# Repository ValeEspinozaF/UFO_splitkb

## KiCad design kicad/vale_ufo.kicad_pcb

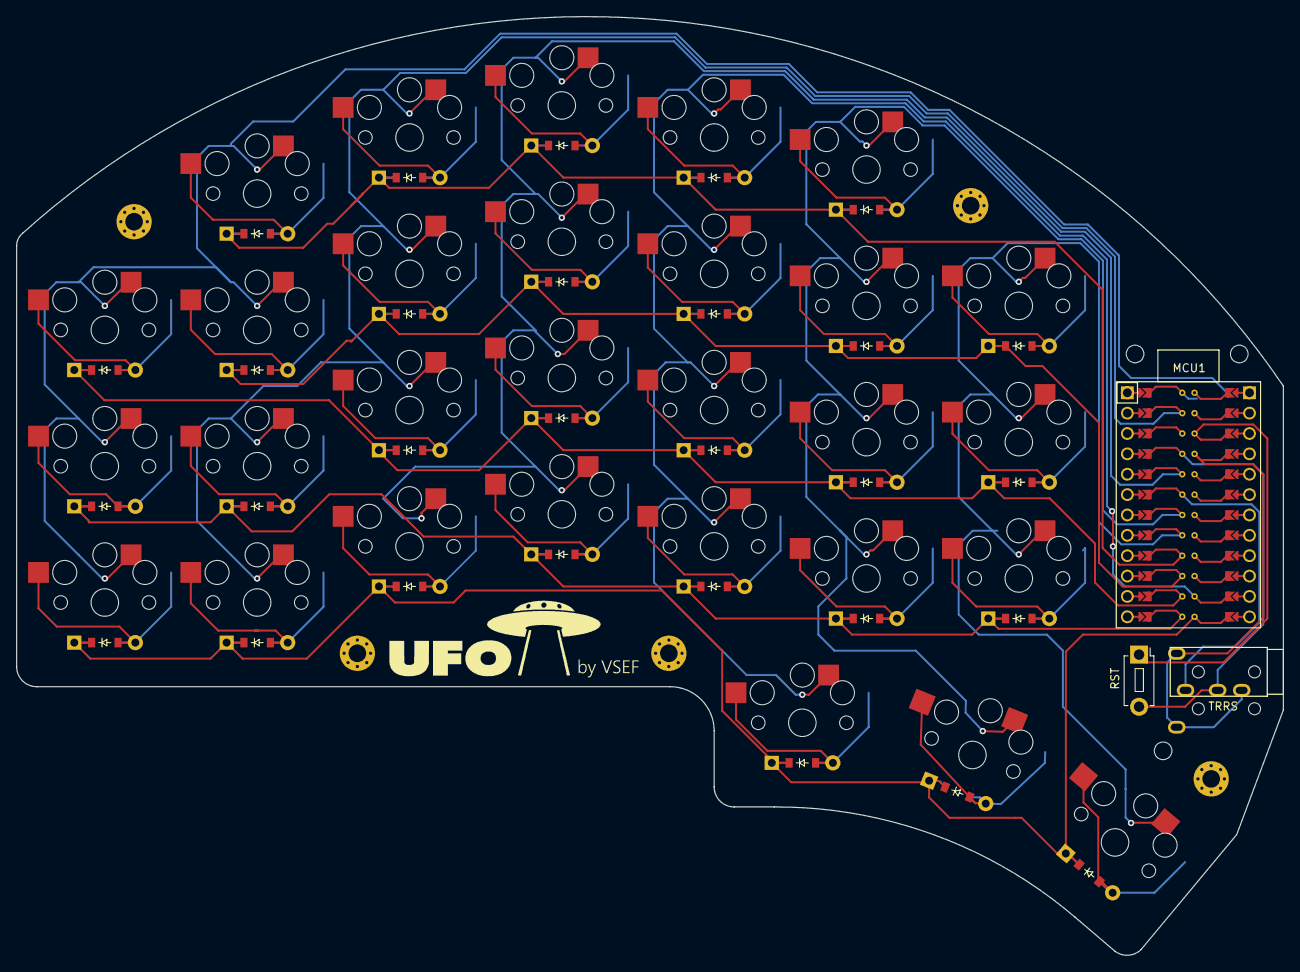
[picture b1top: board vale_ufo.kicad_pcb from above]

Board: 2 copper layers, 158.0 x 117.1 mm, 61 parts (0 on the bottom side), 44 nets.

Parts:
D1, D2, D3, D4, D5, D6, D7, D8, D9, D10, D11, D12, D13, D14, D15, D16, D17, D18, D19, D20, D21, D22, D23, D24, D25, D26, D27, D28, D29: ComboDiode
MCU1: ProMicro
RST: SW_PUSH_1P1T_6x3.5mm_H4.3_APEM_MJTP1243
S1, S2, S3, S4, S5, S6, S7, S8, S9, S10, S11, S12, S13, S14, S15, S16, S17, S18, S19, S20, S21, S22, S23, S24, S25, S26, S27, S28, S29: PG1350
TRRS: TRRS-PJ-320A-dual

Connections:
GND: MCU1.2, MCU1.21, MCU1.22, RST.2, TRRS.3
P0: MCU1.23, S4.1, S5.1, S9.1, S10.1, S11.1
P1: MCU1.24, S1.1, S2.1, S3.1, S6.1, S7.1
P2: MCU1.20, S8.1, S12.1, S13.1, S14.1, S15.1
P3: MCU1.19, TRRS.2
P4: MCU1.18, S20.1, S21.1, S22.1, S23.1, S28.1
P5: MCU1.17, S24.1, S25.1, S26.1, S29.1
P6: D7.1, D7.2, D11.1, D11.2, D15.1, D15.2, D19.1, D19.2, D23.1, D23.2, MCU1.16
P7: D6.1, D6.2, D10.1, D10.2, D14.1, D14.2, D18.1, D18.2, D22.1, D22.2, D26.1, D26.2, MCU1.15
P8: D3.1, D3.2, D9.1, D9.2, D13.1, D13.2, D17.1, D17.2, D21.1, D21.2, D25.1, D25.2, MCU1.14
P9: D2.1, D2.2, D5.1, D5.2, D12.1, D12.2, D16.1, D16.2, D20.1, D20.2, D24.1, D24.2, MCU1.13
P10: D1.1, D1.2, D4.1, D4.2, D8.1, D8.2, D27.1, D27.2, D28.1, D28.2, D29.1, D29.2, MCU1.12
P16: MCU1.11, S16.1, S17.1, S18.1, S19.1, S27.1
RST: MCU1.3, RST.1
VCC: MCU1.4, TRRS.1, TRRS.4
far_thumb: D29.1, D29.2, S29.2
home_thumb: D28.1, D28.2, S28.2
index2_bottom: D20.1, D20.2, S20.2
index2_home: D21.1, D21.2, S21.2
index2_home2: D22.1, D22.2, S22.2
index2_top: D23.1, D23.2, S23.2
index_bottom: D16.1, D16.2, S16.2
index_home: D17.1, D17.2, S17.2
index_home2: D18.1, D18.2, S18.2
index_top: D19.1, D19.2, S19.2
inner_bottom: D24.1, D24.2, S24.2
inner_home: D25.1, D25.2, S25.2
inner_home2: D26.1, D26.2, S26.2
middle_bottom: D12.1, D12.2, S12.2
middle_home: D13.1, D13.2, S13.2
middle_home2: D14.1, D14.2, S14.2
middle_top: D15.1, D15.2, S15.2
near_thumb: D27.1, D27.2, S27.2
outer_bottom: D1.1, D1.2, S1.2
outer_home: D2.1, D2.2, S2.2
outer_home2: D3.1, D3.2, S3.2
pinky_bottom: D4.1, D4.2, S4.2
pinky_home: D5.1, D5.2, S5.2
pinky_home2: D6.1, D6.2, S6.2
pinky_top: D7.1, D7.2, S7.2
ring_bottom: D8.1, D8.2, S8.2
ring_home: D9.1, D9.2, S9.2
ring_home2: D10.1, D10.2, S10.2
ring_top: D11.1, D11.2, S11.2
